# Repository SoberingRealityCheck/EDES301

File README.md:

# EDES301

Repository for my Spring 2026 'EDES 301 - Introduction to Practical Electrical Engineering' classwork.

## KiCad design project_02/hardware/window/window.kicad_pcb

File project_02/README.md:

# Window to Another World

This repo contains the KiCAD Project files for my 'Window to Another World' EDES 310 PCB project.

# Project Overview

The Window is a device intended for art programs / simple games - it runs a linux system with a custom LED matrix display and connections to an IMU, a buzzer, and four buttons.

This repo contains the KiCAD project files for the full system on one chip. 

# Board Specifics

The board is a four-layer PCB with a custom design intended to be mounted directly below the LED Matrix and span the full width of the device. 

The board connects to the display via two cable ports: the 2x08 male header for our 16 data cables and the screw terminals for power and ground.

The IMU communicates via I2C, while the buzzer is driven via PWM and the buttons are simple pull-up GPIO inputs.

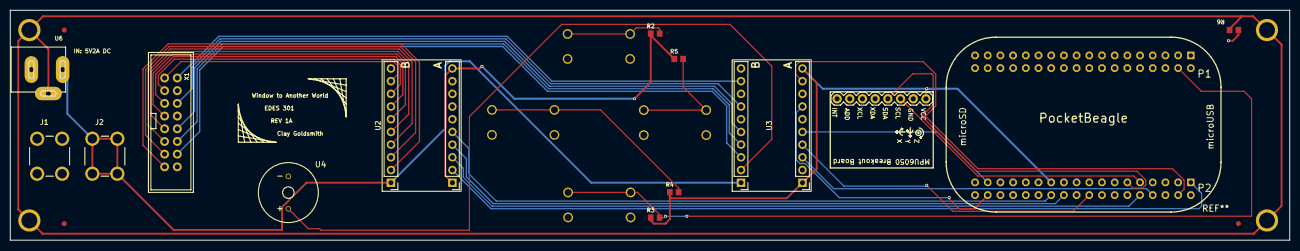
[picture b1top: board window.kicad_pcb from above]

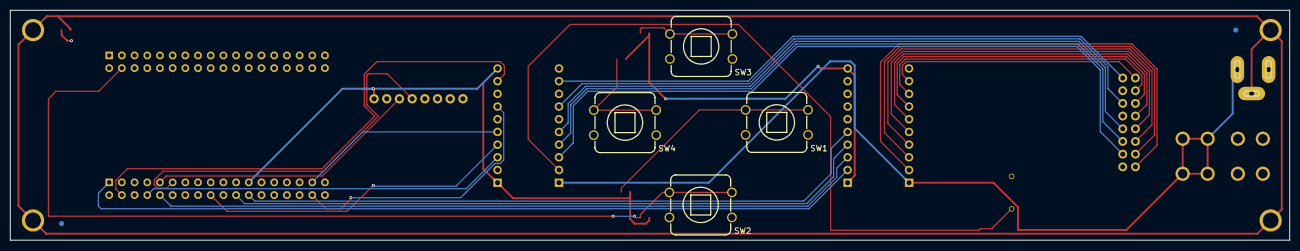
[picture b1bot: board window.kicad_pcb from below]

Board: 4 copper layers, 256.0 x 46.0 mm, 27 parts (6 on the bottom side), 38 nets.

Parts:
FUD2, FUD3, FUD4, FUD5, FUD6: FIDUCIAL_40MIL
J1, J2: 7696; KEYSTONE_7696
M1, M2, M3, M4: MOUNTING_HOLE
R2, R3, R4, R5, R6: R0805
SW1, SW2, SW3, SW4: BUTTON_12.5MM
U1: POCKETBEAGLE
U2, U3: EP-TXS0-108E
U4: BUZZER_6.5MM
U5: MPU6050 Breakout Board
U6: DCJACK_2MM_PTH
X1: 2X08_SHROUDED

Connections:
+3V3: R2.1, R3.1, R4.1, R5.1, U1.P2_23 (3.3V@2), U2.OE, U2.VCCA, U3.OE, U3.VCCA, U5.1 (VCC)
+5V: J2.1_1 (1), J2.1_2 (1), J2.1_3 (1), J2.1_4 (1), U1.P1_14 (3.3V@1), U2.VCCB, U3.VCCB, U6.+5V
/BUTTON_B: R3.2, SW2.1, SW2.3, U1.P1_04 (GPIO89)
/BUTTON_L: R4.2, SW1.1, SW1.3, U1.P1_02 (AIN6(3.3V)GPIO87)
/BUTTON_R: R5.2, SW4.1, SW4.3, U1.P1_08 (SPI0.CLK)
/BUTTON_S: R2.2, SW3.1, SW3.3, U1.P1_06 (SPI0.CS)
/BUZZER: U1.P1_12 (SPI0.MOSI), U3.A1
/I2C_SCL: U1.P2_09 (I2C1.SCL), U5.3 (SCL)
/I2C_SDA: U1.P2_11 (I2C1.SDA), U5.4 (SDA)
/LED_BLUE1: U1.P2_06 (GPIO57), U2.A7
/LED_BLUE2: U1.P1_20 (GPIO20), U2.A5
/LED_CLOCK: U1.P2_10 (GPIO52), U2.A2
/LED_GREEN1: U1.P2_04 (GPIO58), U3.A8
/LED_GREEN_2: U1.P2_34 (PRU0.5), U3.A6
/LED_LATCH: U1.P2_08 (GPIO60), U3.A2
/LED_OUTPUT_ENABLE: U1.P2_01 (PWM1A), U2.A1
/LED_RED1: U1.P2_02 (GPIO59), U2.A8
/LED_RED2: U1.P2_03 (GPIO23), U2.A6
/LED_SELECT_A: U1.P2_24 (GPIO44), U2.A4
/LED_SELECT_B: U1.P2_33 (GPIO45), U3.A4
/LED_SELECT_C: U1.P2_22 (GPIO46), U2.A3
/LED_SELECT_D: U1.P2_18 (GPIO47), U3.A3
GND: J1.1_1 (1), J1.1_2 (1), J1.1_3 (1), J1.1_4 (1), R6.2, SW1.2, SW1.4, SW2.2, SW2.4, SW3.2, SW3.4, SW4.2, SW4.4, U1.P1_16 (GND@2), U1.P1_22 (GND@3), U1.P2_15 (GND@4), U1.P2_21 (GND@5), U2.GND, U3.GND, U4.-, U5.2 (GND), U6.GND, X1.4 (GND), X1.8 (GND), X1.16 (GND)
GNDPWR: M1.1 (1_1), M2.1 (1_1), M3.1 (1_1), M4.1 (1_1), R6.1, U6.GNDPWR
unnamed: U3.B1, U4.+
unnamed: U2.B4, X1.9 (A)
unnamed: U2.B7, X1.3 (B1)
unnamed: U2.B5, X1.7 (B2)
unnamed: U3.B4, X1.10 (B)
unnamed: U2.B3, X1.11 (C)
unnamed: U2.B2, X1.13 (CLK)
unnamed: U3.B3, X1.12 (D)
unnamed: U3.B8, X1.2 (G1)
unnamed: U3.B6, X1.6 (G2)
unnamed: U3.B2, X1.14 (LAT)
unnamed: U2.B1, X1.15 (OE)
unnamed: U2.B8, X1.1 (R1)
unnamed: U2.B6, X1.5 (R2)

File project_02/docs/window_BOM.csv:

"Reference","Qty","Footprint","MANUFACTURER","Description"
"FUD1,FUD2,FUD3,FUD4,FUD5,FUD6","6","combo_lock:FIDUCIAL_40MIL","-","-"
"J1,J2","2","7696","Keystone Electronics","7696 M3 Screw Terminal"
"M1,M2,M3,M4","4","combo_lock:MOUNTING_HOLE","-","Chassis Mounting Hole w/GND connection ability"
"R2,R3,R4,R5,R6","5","combo_lock:R0805","-","RESISTOR, American symbol"
"SW1,SW2,SW3,SW4","4","combo_lock:BUTTON_12.5MM","-","Generic Button"
"U1","1","combo_lock:POCKETBEAGLE","BeagleBoard.org","Pocket Beagle"
"U2,U3","2","Window:EP-TXS0-108E","EPLZON","TXSO108E Bidirectional Logic Shifter Breakout Board"
"U4","1","combo_lock:BUZZER_6.5MM","YUEXIN","Analog Buzzer"
"U5","1","Window:MPU6050 Breakout Board","AITRIP","MPU6050 Breakout Board"
"U6","1","Window:DCJACK_2MM_PTH","Adafruit","2.1mm DC Jack (preferably connected to a 5V2A supply)"
"X1","1","Window:2X08_SHROUDED","Adafruit","Shrouded 2x08 Male Header"

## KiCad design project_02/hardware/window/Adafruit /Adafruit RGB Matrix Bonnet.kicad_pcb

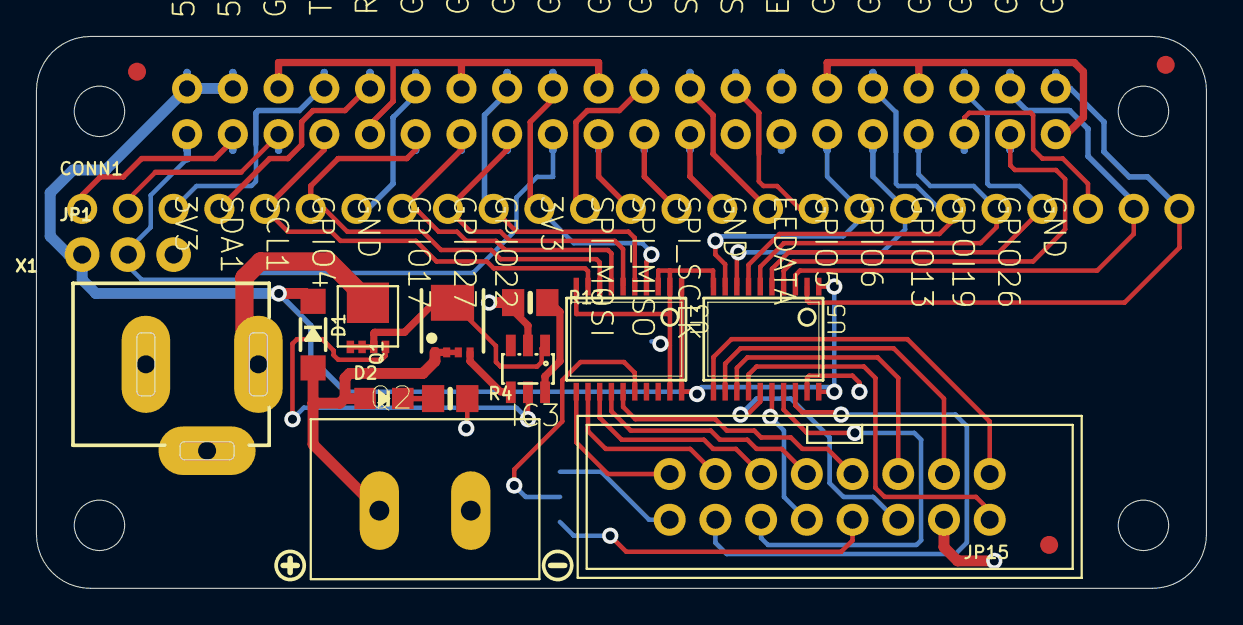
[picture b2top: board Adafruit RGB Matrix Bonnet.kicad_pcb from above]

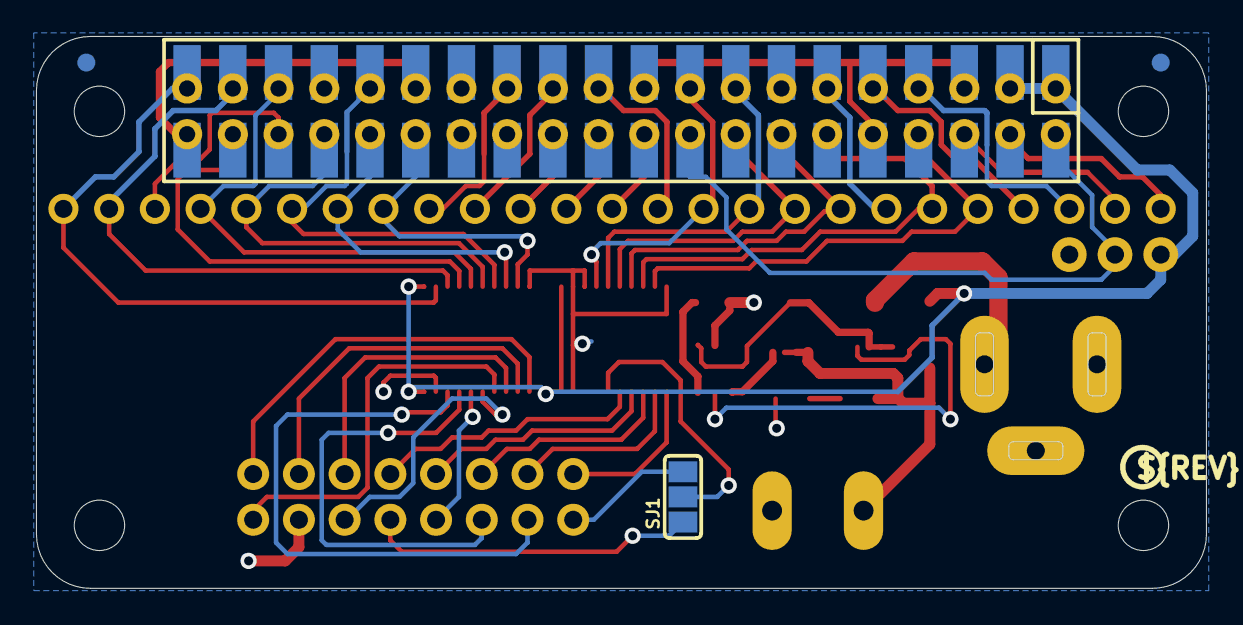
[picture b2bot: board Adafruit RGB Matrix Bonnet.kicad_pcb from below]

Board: 2 copper layers, 65.0 x 30.7 mm, 24 parts (3 on the bottom side), 54 nets.

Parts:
CONN1: HEADER-1X25; 1X25_ROUND_70MIL
D1: MBR120; SOD-123
D2: green; CHIPLED_0805_NOOUTLINE
FID1, FID2, FID3: FIDUCIAL_1MM
IC3: MAX4866T; SOT23-6
JP1: 1X03_ROUND_76
JP15: 2X08_SHROUDED
MATRIX_PWR0: PINHEAD; TERMBLOCK508
Q1: AON3414; POWERPAK-1212-8
Q2: AON7401; POWERDI3333
R4, R13: 1K; 0805-NO
RPI1: RASPBERRYPI_BPLUS_BONNET_THMSMT; PI_BONNET_THMSMT
SJ1: SOLDERJUMPER_2WAY_OPEN_NOPASTE
U3, U5: 74AHCT245; TSSOP20
U$1: BONNET_MATRIX_TOP
U$3: PCBFEAT-REV-056
U$6: BONNET_MATRIX_BOT
U$10: SYMBOL_PLUS
U$11: SYMBOL_MINUS
X1: 2.1mm DC; DCJACK_2MM_PTH

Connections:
3.3V: JP1.2, RPI1.1, RPI1.17, RPI1.S1, RPI1.S17
5.0V: D1.A, D2.A, MATRIX_PWR0.P$4, Q1.1, Q1.2, Q1.3
5VIN: Q2.5678, X1.PWR
+5V: D1.C, JP1.1, RPI1.2, RPI1.4, RPI1.S2, RPI1.S4, U3.1, U3.20, U5.1, U5.20
CLK: JP15.13, U3.12
EECLK: RPI1.28, RPI1.S28
EEDATA: RPI1.27, RPI1.S27
GND: IC3.2, JP1.3, JP15.4, MATRIX_PWR0.P$3, R4.2, R13.1, RPI1.6, RPI1.9, RPI1.14, RPI1.20, RPI1.25, RPI1.30, RPI1.34, RPI1.39, RPI1.S6, RPI1.S9, RPI1.S14, RPI1.S20, RPI1.S25, RPI1.S30, RPI1.S34, RPI1.S39, U3.2, U3.3, U3.10, U3.19, U5.10, U5.19, X1.GND, X1.GNDBREAK
GPIO4: CONN1.5, RPI1.7, RPI1.S7, U3.9
GPIO5: CONN1.18, RPI1.29, RPI1.S29, U5.9
GPIO6: CONN1.19, RPI1.31, RPI1.S31, U5.8
GPIO12: CONN1.20, RPI1.32, RPI1.S32, U5.7
GPIO13: CONN1.21, RPI1.33, RPI1.S33, U5.6
GPIO16: CONN1.22, RPI1.36, RPI1.S36, U5.5
GPIO17: CONN1.6, RPI1.11, RPI1.S11, U3.8
GPIO18: CONN1.7, RPI1.12, RPI1.S12
GPIO19: CONN1.23, RPI1.35, RPI1.S35
GPIO20: CONN1.24, RPI1.38, RPI1.S38, U5.3
GPIO21: CONN1.25, RPI1.40, RPI1.S40, U5.2
GPIO22: CONN1.9, RPI1.15, RPI1.S15, U3.6
GPIO23: CONN1.10, RPI1.16, RPI1.S16, U3.5
GPIO24: CONN1.11, RPI1.18, RPI1.S18, U3.4
GPIO25: CONN1.12, RPI1.22, RPI1.S22
GPIO26: RPI1.37, RPI1.S37, U5.4
GPIO27: CONN1.8, RPI1.13, RPI1.S13, U3.7
LAT: JP15.14, U5.18
M1_A: JP15.9, U3.14
M1_B: JP15.10, U5.16
M1_B1: JP15.3, U5.12
M1_B2: JP15.7, U3.15
M1_C: JP15.11, U3.13
M1_D: JP15.12, U5.17
M1_E: SJ1.2, U3.16
M1_E': JP15.8, SJ1.1
M1_E'': JP15.16, SJ1.3
M1_G1: JP15.2, U5.14
M1_G2: JP15.6, U5.15
M1_R1: JP15.1, U5.11
M1_R2: JP15.5, U5.13
unnamed: IC3.6, R13.2
unnamed: D2.C, R4.1
unnamed: IC3.1, Q1.5-8, Q2.1, Q2.2, Q2.3
unnamed: IC3.4, Q1.4
unnamed: IC3.5, Q2.4
OE: JP15.15, U3.11
RXD: CONN1.4, RPI1.10, RPI1.S10
SCL: CONN1.2, RPI1.5, RPI1.S5
SDA: CONN1.1, RPI1.3, RPI1.S3
SPI_CE0: CONN1.16, RPI1.24, RPI1.S24
SPI_CE1: CONN1.17, RPI1.26, RPI1.S26
SPI_MISO: CONN1.14, RPI1.21, RPI1.S21
SPI_MOSI: CONN1.13, RPI1.19, RPI1.S19
SPI_SCLK: CONN1.15, RPI1.23, RPI1.S23
TXD: CONN1.3, RPI1.8, RPI1.S8

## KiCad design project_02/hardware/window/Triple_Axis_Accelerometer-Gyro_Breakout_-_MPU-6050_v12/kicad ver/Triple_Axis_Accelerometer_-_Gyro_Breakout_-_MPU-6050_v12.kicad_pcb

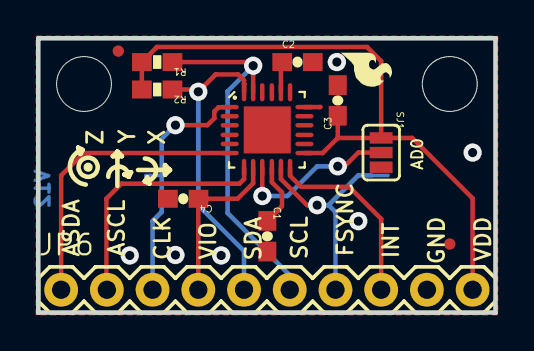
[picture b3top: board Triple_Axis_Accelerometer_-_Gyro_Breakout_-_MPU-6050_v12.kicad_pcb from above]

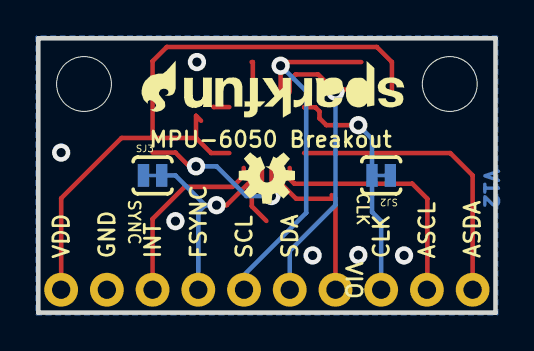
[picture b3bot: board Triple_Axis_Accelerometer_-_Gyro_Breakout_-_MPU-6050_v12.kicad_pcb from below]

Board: 2 copper layers, 25.4 x 15.2 mm, 21 parts (5 on the bottom side), 13 nets.

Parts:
C1, C3: 0.1uF; 0603-CAP
C2: 2.2nF; 0603-CAP
C4: 10nF; 0603-CAP
FRAME1: FRAME-LETTER; CREATIVE_COMMONS
JP2, JP5: FIDUCIALUFIDUCIAL; MICRO-FIDUCIAL
JP3, JP4: STAND-OFFTIGHT; STAND-OFF-TIGHT
JP6: M10"; 1X10
R1, R2: 10k; 0603-RES
SJ1: SJ_3_PASTE2&3
SJ2, SJ3: SJ_2S-TRACE
U1: MPU-6050-1; QFN-24-4MM2
U$1: OSHW-LOGOS; OSHW-LOGO-S
U$2, U$3: SFE-LOGO-FLAME
U$4: SFE-NEW-WEB
U$5: REVISION

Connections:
ADO: SJ1.2, U1.9
AUX_SCL: JP6.2, U1.7
AUX_SDA: JP6.1, U1.6
CLKIN: JP6.3, SJ2.2, U1.1
FSYNC: JP6.7, SJ3.2, U1.11
GND: C1.2, C2.2, C3.2, C4.2, JP6.9, SJ1.3, SJ2.1, SJ3.1, U1.18
INT: JP6.8, U1.12
unnamed: C2.1, U1.20
unnamed: C1.1, U1.10
SCL: JP6.6, R1.1, U1.23
SDA: JP6.5, R2.1, U1.24
VCC: C3.1, JP6.10, R1.2, R2.2, SJ1.1, U1.13
VIO: C4.1, JP6.4, U1.8

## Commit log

2026-02-05 updating README.md
2026-02-18 assignment 03
2026-02-18 dotfiles and scripts
2026-02-23 Beginnings of Project 1
2026-02-24 added simplecalc.py from class
2026-02-24 filled in class calculator demo code
2026-02-24 added more operators and python 2 compatibility
2026-02-24 amazing LED script
2026-02-24 button updates
2026-02-24 some overrides to prevent my laptop python install from labeling adafruit libraries as missing
2026-03-04 display drivers
2026-03-04 updated display implementation
2026-03-04 fixed typo
2026-03-04 clay is cool
2026-03-04 full i2cset path
2026-03-04 syntax
2026-03-04 initializing peoplecounter
2026-03-04 updated documentation
2026-03-04 people counter beginnings
2026-03-04 people counter continuings
2026-03-04 people counter completings
2026-03-04 button activation
2026-03-04 some sketching of project software architecture
2026-03-06 potentiometer
2026-03-06 finished potentiometer
2026-03-06 servo
2026-03-26 yeah
2026-04-01 big software infrastructure for app commit
2026-04-01 flipped zoom settings in glass app
2026-04-02 buzzer
2026-04-02 docstring tweaks
2026-04-02 some buzzer sfx improvements
2026-04-02 shell script (vague idea)
2026-04-02 some hardware driver progress
2026-04-18 big steps towards final hardware integration yippee. new display size update
2026-04-22 pyledscape
2026-04-22 actual hardware pin assignments
2026-04-22 added pyledscape to python path
2026-04-22 ok actually added pyledscape
2026-04-22 pyledscape context matrix please work
2026-04-22 i am an idiot. and state machines are hard
2026-04-22 pyledscape is picky about pins
2026-04-22 i'm stupid and the button pins were totally wrong
2026-04-22 our button config was reversed
2026-04-22 add better button debug info dammit
2026-04-22 misc fixes
2026-04-22 i love debugging
2026-04-22 buttons...
2026-04-22 please fix the display now lmao
2026-04-22 BUTTON DEBUGGING INFO
2026-04-22 lol buzzer pin was still placeholder
2026-04-22 fixed buzzer pin AGAIN
2026-04-22 pin 36?
2026-04-22 fixed old pin assignments again
2026-04-23 IMU integration?
2026-04-24 cron path fix
2026-05-06 massive project 2 commit
2026-05-06 presentation format
2026-05-06 Clarify project as PCB in README
    Updated project description to specify PCB.
2026-05-06 add new image
2026-05-06 Change image in README to 3D render
    Updated image reference in README from front view to 3D render.
2026-05-06 Add Gerber image to project README
    Added a Gerber image to the README for better visualization.

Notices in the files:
parts and their libraries:
Released under the Creative Commons Attribution Share-Alike 3.0 License
http://creativecommons.org/licenses/by-sa/3.0
